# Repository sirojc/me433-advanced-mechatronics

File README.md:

# ME433_Joris
*ME433 Advanced Mechatronics* repository of Joris Chomarat

Spring 2023 @ Northwestern University

This repository contains the code deliverables for all assignments, to be found [here](https://github.com/ndm736/ME433_2023/wiki/Schedule). 

### Assignments
#### [HW2](HW2/) - 3.3V regulator, PIC32
[Assignment 2](https://github.com/ndm736/ME433_2023/wiki/HW2)
- Built a 3.3V regulator, to be able to power the PIC32 microchip and other sensors at 3.3V. Power comes from 5V (USB) or 6V (Battery Pack). A switch enables to change powering method, shown on the PCB in [HW4](/HW4).
- Connected the PIC32 microchip and LEDs to the circuit and wrote a loop to blink 2 LEDs in a certain frequency.

#### [HW3](HW3/HW3_send_sin.X) - USB to UART
[Assignment 3](https://github.com/ndm736/ME433_2023/wiki/HW3)
- Wrote a loop to send a sine wave from the PIC32 to a PC over UART communication at eveery push of a button in the circuit.

#### [HW4](HW4/) - PCB Design
[Assignment 4](https://github.com/ndm736/ME433_2023/wiki/HW4)
- Designed a PCB from scratch to use in the final [robot](/HW16)
- Used the same components as for previous assignments, as well as a power switch and holes for header pins to connect further PCBs on top later.

#### [HW5](HW5/) - SPI
[Assignment 5](https://github.com/ndm736/ME433_2023/wiki/HW5)
- Used SPI to write to an MCP4912 and send a sine and triangle wave.

#### [HW6](HW6/HW6_I2C.X) - I2C
[Assignment 6](https://github.com/ndm736/ME433_2023/wiki/HW6)
- Used I2C to communicate with an MCP23008. Made an LED blink at the push of a button, communicated through IC2.

#### [HW7](HW7/) - IMU
[Assignment 7](https://github.com/ndm736/ME433_2023/wiki/HW7)
- Read sensor measurements from an inertial measurement unit and plotted the x acceleration using I2C and UART.

#### [HW8](HW8/) - OLED Display
[Assignment 8](https://github.com/ndm736/ME433_2023/wiki/HW8)
- Printed z acceleration measurements from the IMU in [HW7](/HW7) to an OLED display.

#### [HW9](HW9/) - DSP
[Assignment 9](https://github.com/ndm736/ME433_2023/wiki/HW9)
- Digital Signal Processing on different data recordings using moving average, IIR, FIR to filter the signals, as well as performing FFT. A couple of plots are shown, the remainder of all plots can be found [here](HW9/plots).

#### [HW10](HW10/) - RGB LED Array
[Assignment 10](https://github.com/ndm736/ME433_2023/wiki/HW10)
- Made a WS2812B LED array display a moving rainbow.

#### [HW11](HW11/) - RPi Pico FFT
[Assignment 11](https://github.com/ndm736/ME433_2023/wiki/HW11)
- Overlayed 3 sine waves and FFT filtered them in CircuitPython on a Raspberry Pi Pico W.
- Transmitted the filtered wave via UART.

#### [HW13](HW13/) - RPi Pico Website
[Assignment 13](https://github.com/ndm736/ME433_2023/wiki/HW13)
- Hosted a website on a Raspberry Pi Pico W.
- Displayed the time elapsed between two button pushes on the website.

#### [HW14](HW14/) - Servo Motor
[Assignment 14](https://github.com/ndm736/ME433_2023/wiki/HW14)
- Used PWM to control an Rc servo motor.

#### [HW15](HW15/) - Camera Line Detection
[Assignment 15](https://github.com/ndm736/ME433_2023/wiki/HW15)
- Developed an algorithm to detect the middle of a line of changing color (map shown [here](https://github.com/ndm736/ME433_2023/wiki/HW16).
- Best results were achieved by converting the image to grayscale and estimating the middle of the line based on brightness.
- Visualized detection results from the recorded image on the OLED display from [HW8](/hw8).

#### [HW16](HW16/) - Line following robot
[Assignment 16](https://github.com/ndm736/ME433_2023/wiki/HW16)
- Assembled a robot with custom 3D-printed and lasercutted parts and made it follow a line of changing color and curvature. 
- Tuned a PI controller to improve line following capabilities.
- Robot was able to follow a straight line, even of changing color, fairly well. Turns, however, did not work well.

### Tips
- Connect to PIC via screen (on mac) with a baudrate of ```230400```.

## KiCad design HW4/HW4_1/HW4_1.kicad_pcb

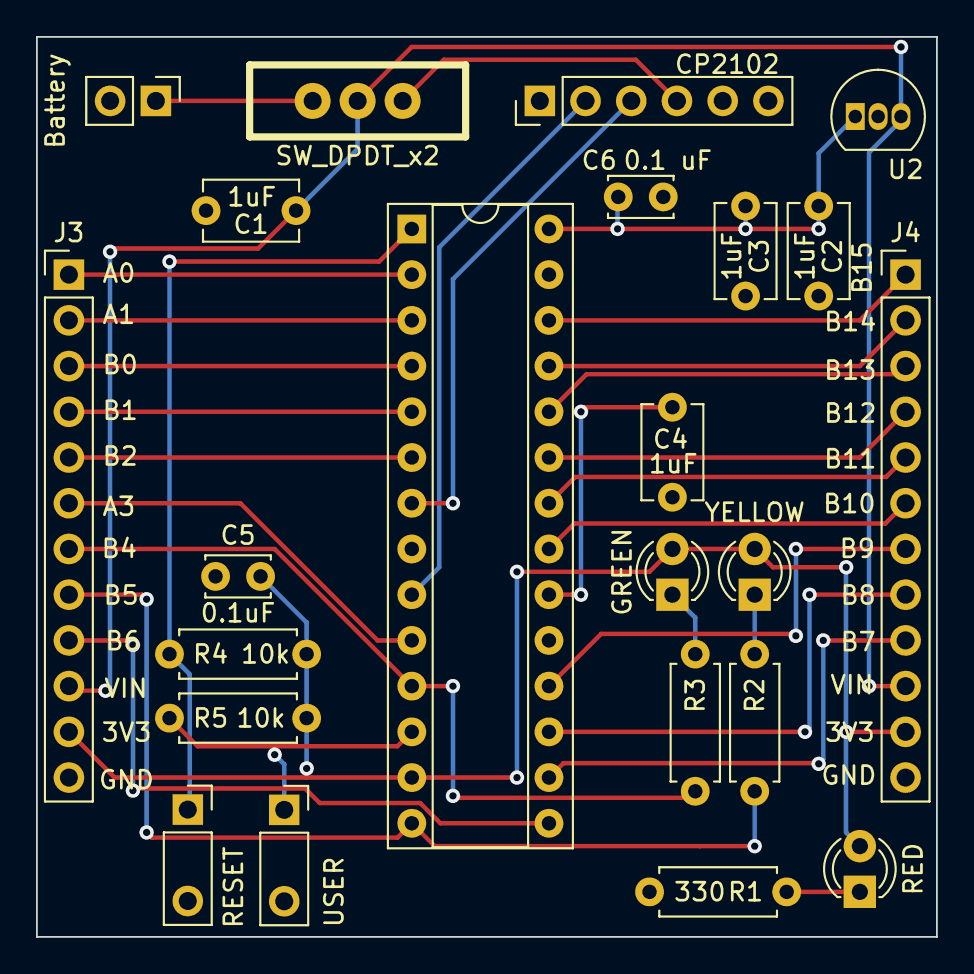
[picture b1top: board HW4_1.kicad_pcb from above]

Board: 2 copper layers, 50.0 x 50.0 mm, 23 parts (0 on the bottom side), 31 nets.

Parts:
C1, C2, C3, C4: 1uF; C_Disc_D5.1mm_W3.2mm_P5.00mm
C5: 0.1uF; C_Disc_D3.4mm_W2.1mm_P2.50mm
C6: 0.1 uF; C_Disc_D3.4mm_W2.1mm_P2.50mm
CP2102: CP2102N; PinHeader_1x06_P2.54mm_Vertical
D1: RED; LED_D3.0mm
D2: YELLOW; LED_D3.0mm
D3: GREEN; LED_D3.0mm
J2: Battery; PinHeader_1x02_P2.54mm_Vertical
J3, J4: Conn_01x12_Pin; PinHeader_1x12_P2.54mm_Vertical
R1, R2, R3: 330; R_Axial_DIN0207_L6.3mm_D2.5mm_P7.62mm_Horizontal
R4, R5: 10k; R_Axial_DIN0207_L6.3mm_D2.5mm_P7.62mm_Horizontal
SW1: RESET; pushbutton
SW2: USER; pushbutton
SW3: SW_DPDT_x2; Slideswitch
U1: PIC32MX170F256B; DIP-28_W7.62mm_Socket
U2: AP7381-33Y; TO-92_Inline

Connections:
+3.3V: C2.1, C3.1, C5.2, C6.1, D1.2 (A), D2.2 (A), D3.2 (A), J3.11, J4.11, R4.2, R5.2, U1.13 (Vdd), U1.28 (AVdd), U2.1 (VO)
+5V: CP2102.4, SW3.3 (C)
/A0: J3.1, U1.2 (A0)
/A1: J3.2, U1.3 (A1)
/A3: J3.6, U1.10 (A3)
/A4: R5.1, SW2.1 (A), U1.12 (A4)
/B0: J3.3, U1.4 (B0)
/B1: J3.4, U1.5 (B1)
/B2: J3.5, U1.6 (B2)
/B6: J3.9, U1.15 (B6)
/B7: J4.9, U1.16 (B7)
/B10: J4.6, U1.21 (B10)
/B11: J4.5, U1.22 (B11)
/B12: J4.4, U1.23 (B12)
/B13: J4.3, U1.24 (B13)
/GREEN: J3.7, R3.2, U1.11 (B4)
/MCLR: R4.1, SW1.1 (A), U1.1 (MCLR)
/SCK1-B14: J4.2, U1.25 (SCK1-B14)
/SCK2-B15: J4.1, U1.26 (SCK2-B15)
/SCL1-B8: J4.8, U1.17 (SCL1-B8)
/SDA1-B9: J4.7, U1.18 (SDA1-B9)
/U1RX: CP2102.3, U1.7 (B3)
/U1TX: CP2102.2, U1.9 (A2)
/Vin: C1.1, J3.10, J4.10, SW3.2 (B), U2.3 (VI)
/YELLOW: J3.8, R2.2, U1.14 (B5)
GND: C1.2, C2.2, C3.2, C4.2, C5.1, C6.2, CP2102.6, J2.2, J3.12, J4.12, R1.1, SW1.2 (A), SW2.2 (A), U1.8 (Vss), U1.19 (Vss), U1.27 (AVss), U2.2 (GND)
unnamed: D1.1 (K), R1.2
unnamed: D2.1 (K), R2.1
unnamed: D3.1 (K), R3.1
unnamed: J2.1, SW3.1 (A)
unnamed: C4.1, U1.20 (Vcap)

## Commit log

2023-03-31 generated project for HW2
2023-04-03 user-input blink amount and duration, note on connection establishment
2023-04-03 beautify template.c
2023-04-03 add .DS_Store files to gitignore
2023-04-04 HW3: send sine wave on button press
2023-04-06 completed schematics
2023-04-11 PCB footprint & start of board
2023-04-13 board start routing
    Bug to resolve: Pushbuttons have both pins GND, but assigned correctly in schematic
2023-04-15 2Hz sine and 1 Hz triangle
2023-04-21 implemented I2C HW6
2023-04-21 implemented IMU HW7
2023-04-25 init HW8
2023-04-25 final HW8
2023-04-27 data HW9
2023-04-29 begin HW9
2023-04-29 params tuned except FIRs
2023-04-29 FIR implemented
2023-04-29 cleanup
2023-05-02 implement HW10, Neopixel not yet turning on
2023-05-03 error should be with c[j]. or high/lowtime
2023-05-03 debugging
2023-05-04 high low times probably wrong
2023-05-04 rainbow implemented, flickering not resolved
2023-05-04 small fix for rainbow
2023-05-11 HW11 Pi Pico superimposed sine waves
2023-05-30 PCB finished
2023-05-30 HW13
2023-06-01 HW14 finished
2023-06-07 line finder working ok
2023-06-08 camera to grayscale, robot follows straight
2023-06-08 robot final
2023-09-26 upload final robot image
